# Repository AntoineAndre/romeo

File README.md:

# ROMEO PUTAIN Edition

Staggered 40% QMK and VIA compatible keyboard pcb assembled with only through hole components, including USB Type-C

**New layout to make a 40%+ keyboard, without changing the edge cuts**

Old layout on top and new layout on bottom

**[BOM, Build Guide, and Flashing Information](./doc)**

~~Kits available at [cftkb.com](https://www.cftkb.com)~~

**[Optional High Profile Lasercut Acrylic Case](./case)**

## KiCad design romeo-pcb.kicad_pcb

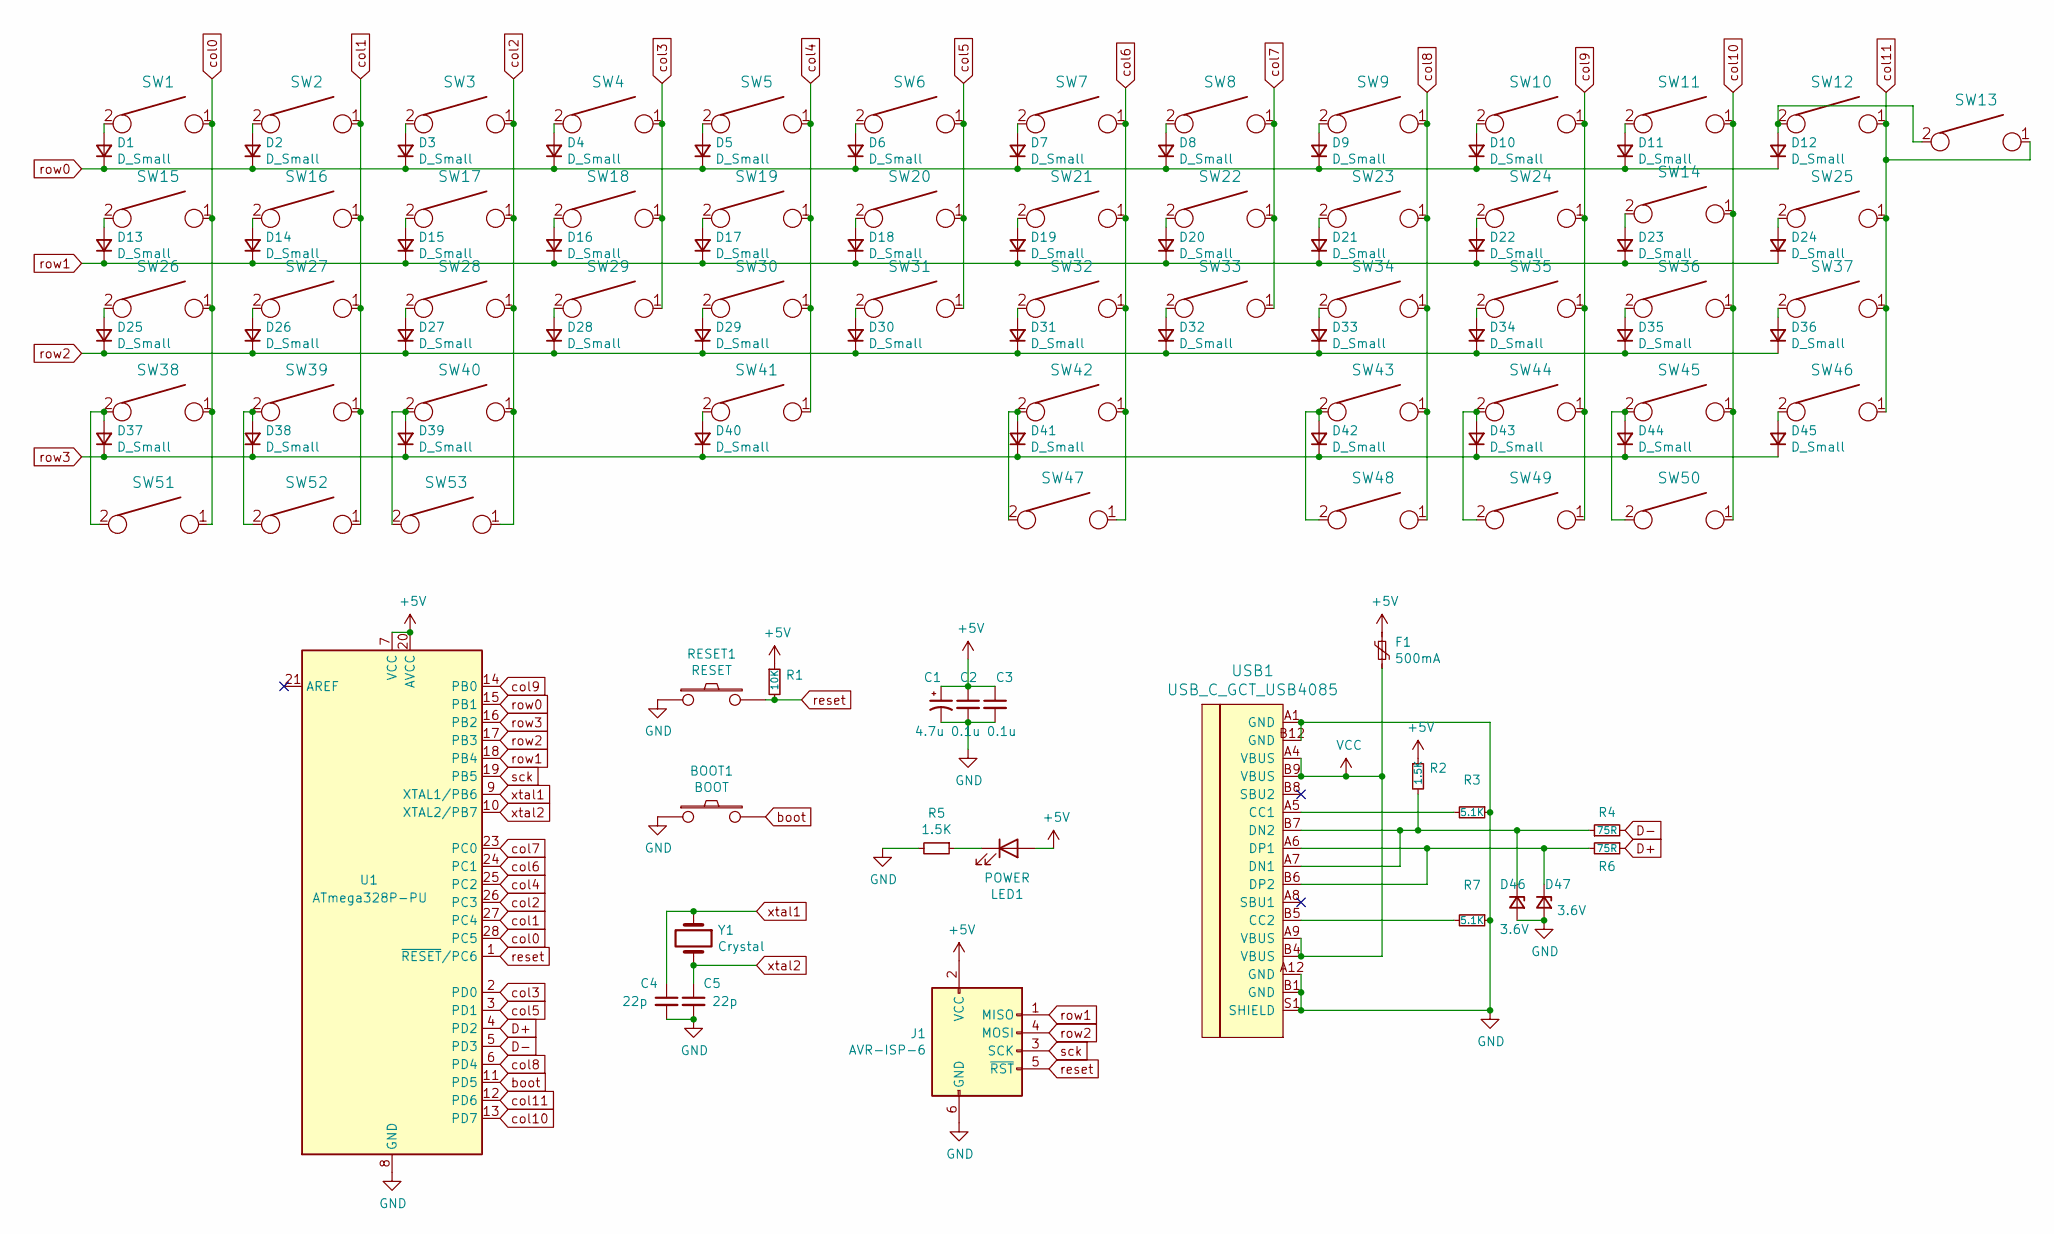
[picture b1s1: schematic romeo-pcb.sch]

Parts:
BOOT1: BOOT; SW_PUSH_6mm
C1: 4.7u; CP_Radial_D4.0mm_P1.50mm
C2, C3: 0.1u; C_Disc_D4.3mm_W1.9mm_P5.00mm
C4, C5: 22p; C_Disc_D3.0mm_W1.6mm_P2.50mm
D1, D2, D3, D4, D5, D6, D7, D8, D9, D10, D11, D12, D13, D14, D15, D16, D17, D18, D19, D20, D21, D22, D23, D24, D25, D26, D27, D28, D29, D30, D31, D32, D33, D34, D35, D36, D37, D38, D39, D40, D41, D42, D43, D44, D45: D_Small; D_DO-35_SOD27_P5.08mm_Horizontal
D46, D47: 3.6V; D_DO-35_SOD27_P5.08mm_Horizontal
F1: 500mA; polyfuse_5.1mm
J1: AVR-ISP-6; AVR_ICSP_3x2
LED1: POWER; LED_D3.0mm
R1: 10K; R_Axial_DIN0204_L3.6mm_D1.6mm_P5.08mm_Horizontal
R2, R5: 1.5K; R_Axial_DIN0204_L3.6mm_D1.6mm_P5.08mm_Horizontal
R3, R7: 5.1K; R_Axial_DIN0204_L3.6mm_D1.6mm_P5.08mm_Horizontal
R4, R6: 75R; R_Axial_DIN0204_L3.6mm_D1.6mm_P5.08mm_Horizontal
RESET1: RESET; SW_PUSH_6mm
SW1, SW2, SW3, SW4, SW5, SW6, SW7, SW8, SW9, SW10, SW11, SW12, SW14, SW16, SW17, SW18, SW19, SW20, SW21, SW22, SW23, SW24, SW27, SW28, SW29, SW30, SW31, SW32, SW33, SW34, SW35, SW36, SW39, SW44, SW46, SW49, SW52, SW53: KEYSW; SW_Cherry_MX1A_1.00u_PCB-NOSCREEN
SW13: KEYSW; SW_Cherry_MX1A_2.00u_PCBNOSCREEN
SW15, SW37, SW48, SW50, SW51: KEYSW; SW_Cherry_MX1A_1.25u_PCBNOSCREEN
SW25, SW26: KEYSW; SW_Cherry_MX1A_1.75u_PCBNOSCREEN
SW38, SW40, SW43, SW45: KEYSW; SW_Cherry_MX1A_1.50u_PCBNOSCREEN
SW41: KEYSW; SW_Cherry_MX1A_2.25u_PCBNOSCREEN
SW42: KEYSW; MXOnly-2.75U-ReversedStabilizers-NoLED
SW47: KEYSW; MXOnly-6.25U-ReversedStabilizers-NoLED
U1: ATmega328P-PU; DIP-28_W7.62mm
USB1: USB_C_GCT_USB4085
Y1: Crystal; Crystal_HC49-4H_Vertical

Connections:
+5V: C1.1, C2.1, C3.1, F1.1, J1.2 (VCC), LED1.2 (A), R1.1, R2.1, U1.7 (VCC), U1.20 (AVCC)
D+: R6.1, U1.4 (PD2)
D-: R4.2, U1.5 (PD3)
GND: BOOT1.1, C1.2, C2.2, C3.2, C4.2, C5.2, D46.2 (A), D47.2 (A), J1.6 (GND), R3.1, R5.2, R7.1, RESET1.1, U1.8 (GND), U1.22 (GND), USB1.A1 (GND), USB1.A12 (GND), USB1.B1 (GND), USB1.B12 (GND), USB1.S1 (SHIELD)
unnamed: D1.2 (A), SW1.2
unnamed: D2.2 (A), SW2.2
unnamed: D3.2 (A), SW3.2
unnamed: D4.2 (A), SW4.2
unnamed: D5.2 (A), SW5.2
unnamed: D6.2 (A), SW6.2
unnamed: D7.2 (A), SW7.2
unnamed: D8.2 (A), SW8.2
unnamed: D9.2 (A), SW9.2
unnamed: D10.2 (A), SW10.2
unnamed: D11.2 (A), SW11.2
unnamed: D12.2 (A), SW12.2, SW13.2
unnamed: D13.2 (A), SW15.2
unnamed: D14.2 (A), SW16.2
unnamed: D15.2 (A), SW17.2
unnamed: D16.2 (A), SW18.2
unnamed: D17.2 (A), SW19.2
unnamed: D18.2 (A), SW20.2
unnamed: D19.2 (A), SW21.2
unnamed: D20.2 (A), SW22.2
unnamed: D21.2 (A), SW23.2
unnamed: D22.2 (A), SW24.2
unnamed: D23.2 (A), SW14.2
unnamed: D24.2 (A), SW25.2
unnamed: D25.2 (A), SW26.2
unnamed: D26.2 (A), SW27.2
unnamed: D27.2 (A), SW28.2
unnamed: D28.2 (A), SW29.2
unnamed: D29.2 (A), SW30.2
unnamed: D30.2 (A), SW31.2
unnamed: D31.2 (A), SW32.2
unnamed: D32.2 (A), SW33.2
unnamed: D33.2 (A), SW34.2
unnamed: D34.2 (A), SW35.2
unnamed: D35.2 (A), SW36.2
unnamed: D36.2 (A), SW37.2
unnamed: D37.2 (A), SW38.2, SW51.2
unnamed: D38.2 (A), SW39.2, SW52.2
unnamed: D39.2 (A), SW40.2, SW53.2
unnamed: D40.2 (A), SW41.2
unnamed: D41.2 (A), SW42.2, SW47.2
unnamed: D42.2 (A), SW43.2, SW48.2
unnamed: D43.2 (A), SW44.2, SW49.2
unnamed: D44.2 (A), SW45.2, SW50.2
unnamed: D45.2 (A), SW46.2
unnamed: D46.1 (K), R2.2, R4.1, USB1.A7 (DN1), USB1.B7 (DN2)
unnamed: D47.1 (K), R6.2, USB1.A6 (DP1), USB1.B6 (DP2)
unnamed: LED1.1 (K), R5.1
unnamed: R3.2, USB1.A5 (CC1)
unnamed: R7.2, USB1.B5 (CC2)
VCC: F1.2, USB1.A4 (VBUS), USB1.A9 (VBUS), USB1.B4 (VBUS), USB1.B9 (VBUS)
boot: BOOT1.2, U1.11 (PD5)
col0: SW1.1, SW15.1, SW26.1, SW38.1, SW51.1, U1.28 (PC5)
col1: SW2.1, SW16.1, SW27.1, SW39.1, SW52.1, U1.27 (PC4)
col2: SW3.1, SW17.1, SW28.1, SW40.1, SW53.1, U1.26 (PC3)
col3: SW4.1, SW18.1, SW29.1, U1.2 (PD0)
col4: SW5.1, SW19.1, SW30.1, SW41.1, U1.25 (PC2)
col5: SW6.1, SW20.1, SW31.1, U1.3 (PD1)
col6: SW7.1, SW21.1, SW32.1, SW42.1, SW47.1, U1.24 (PC1)
col7: SW8.1, SW22.1, SW33.1, U1.23 (PC0)
col8: SW9.1, SW23.1, SW34.1, SW43.1, SW48.1, U1.6 (PD4)
col9: SW10.1, SW24.1, SW35.1, SW44.1, SW49.1, U1.14 (PB0)
col10: SW11.1, SW14.1, SW36.1, SW45.1, SW50.1, U1.13 (PD7)
col11: SW12.1, SW13.1, SW25.1, SW37.1, SW46.1, U1.12 (PD6)
reset: J1.5 (~RST), R1.2, RESET1.2, U1.1 (~RESET~/PC6)
row0: D1.1 (K), D2.1 (K), D3.1 (K), D4.1 (K), D5.1 (K), D6.1 (K), D7.1 (K), D8.1 (K), D9.1 (K), D10.1 (K), D11.1 (K), D12.1 (K), U1.15 (PB1)
row1: D13.1 (K), D14.1 (K), D15.1 (K), D16.1 (K), D17.1 (K), D18.1 (K), D19.1 (K), D20.1 (K), D21.1 (K), D22.1 (K), D23.1 (K), D24.1 (K), J1.1 (MISO), U1.18 (PB4)
row2: D25.1 (K), D26.1 (K), D27.1 (K), D28.1 (K), D29.1 (K), D30.1 (K), D31.1 (K), D32.1 (K), D33.1 (K), D34.1 (K), D35.1 (K), D36.1 (K), J1.4 (MOSI), U1.17 (PB3)
row3: D37.1 (K), D38.1 (K), D39.1 (K), D40.1 (K), D41.1 (K), D42.1 (K), D43.1 (K), D44.1 (K), D45.1 (K), U1.16 (PB2)
sck: J1.3 (SCK), U1.19 (PB5)
xtal1: C4.1, U1.9 (XTAL1/PB6), Y1.1
xtal2: C5.1, U1.10 (XTAL2/PB7), Y1.2

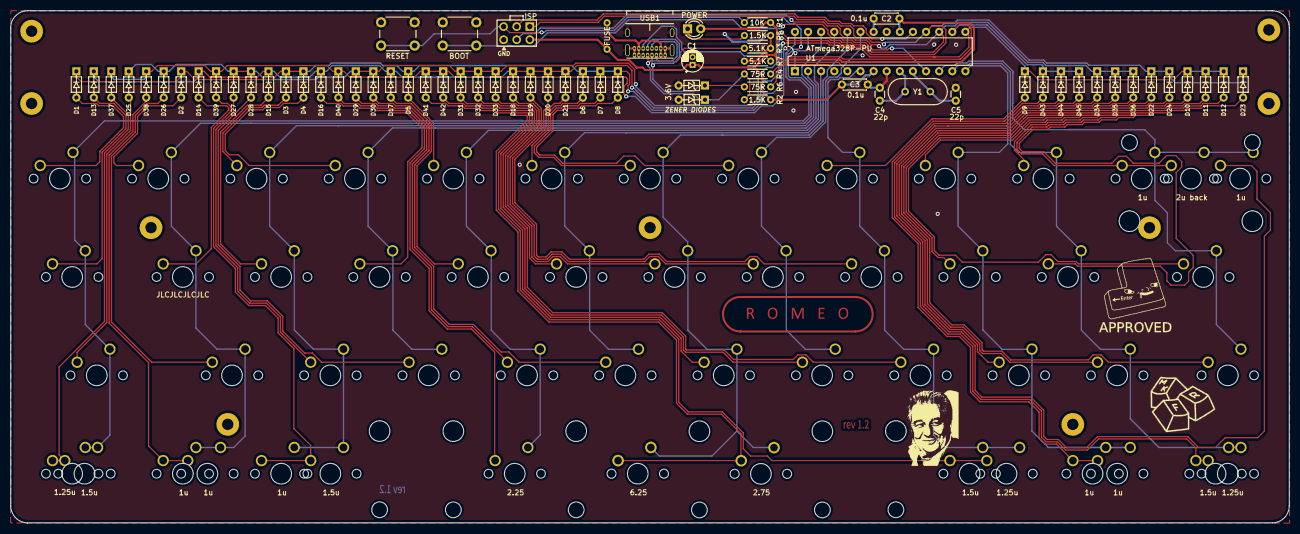
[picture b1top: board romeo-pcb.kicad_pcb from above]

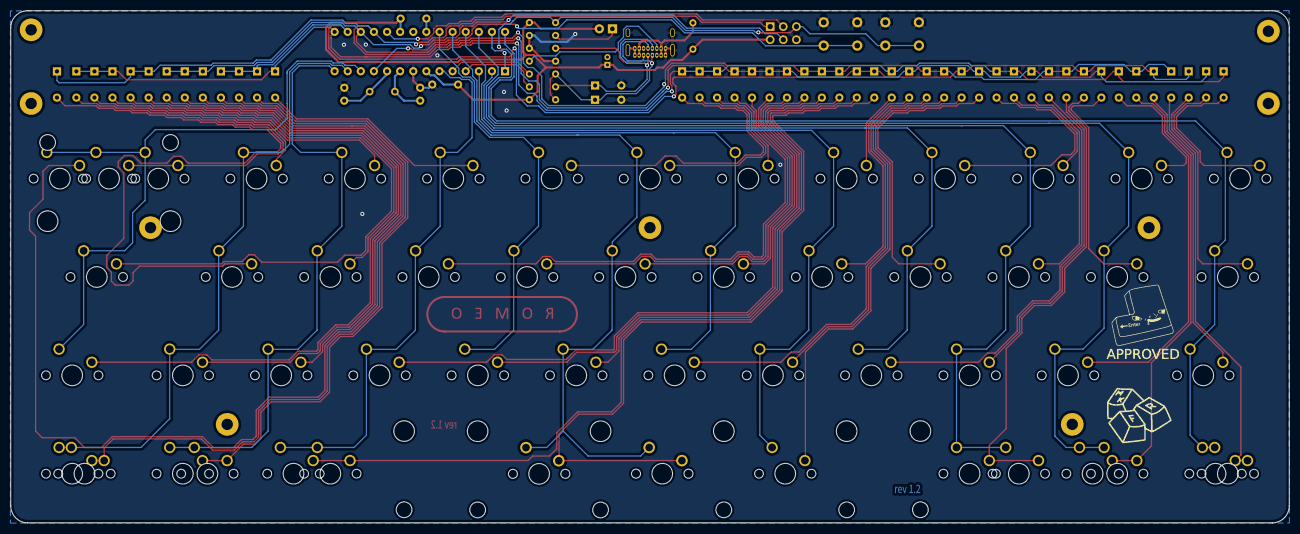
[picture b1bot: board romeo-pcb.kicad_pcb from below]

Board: 2 copper layers, 247.6 x 99.2 mm, 130 parts (5 on the bottom side), 76 nets.

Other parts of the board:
Ref**: Val**; golmon_silk_svg
Ref**#2: Val**; golmon_silk_svg
Ref**#3, Ref**#6: Val**; putain_svg
Ref**#4, Ref**#5: Val**; mkfr_footprint
Ref**#7, Ref**#10: Val**; rev_num
Ref**#8, Ref**#9: Val**; author_footprint

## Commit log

2021-08-11 Add new layout to romeo keyboard
    Add the new layout (based on CC45) to make the keyboard more convenient to use
    Update footprints to match this rev1.2
2021-08-11 Add switch plate
2021-08-16 Update silks and gerbers
2021-08-26 Update gerbers, sent a first command to jlcpcb
2021-09-19 Add firmware putain
2021-11-06 update keymap and firmware with via compat and .hex file
